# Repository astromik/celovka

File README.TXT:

Astronomická čelovka s červeným a bílým regulovatelným světlem, která je řízená pomocí ATtiny25.

Detaily:
  http://www.astromik.org/raspi/celovka

Video s ukázkou činnosti (verze sw 11):
   https://youtu.be/cCZswjiehJQ

Video s doplněnými funkcemi (verze sw 12):
   https://youtu.be/9VESLbRYwD0

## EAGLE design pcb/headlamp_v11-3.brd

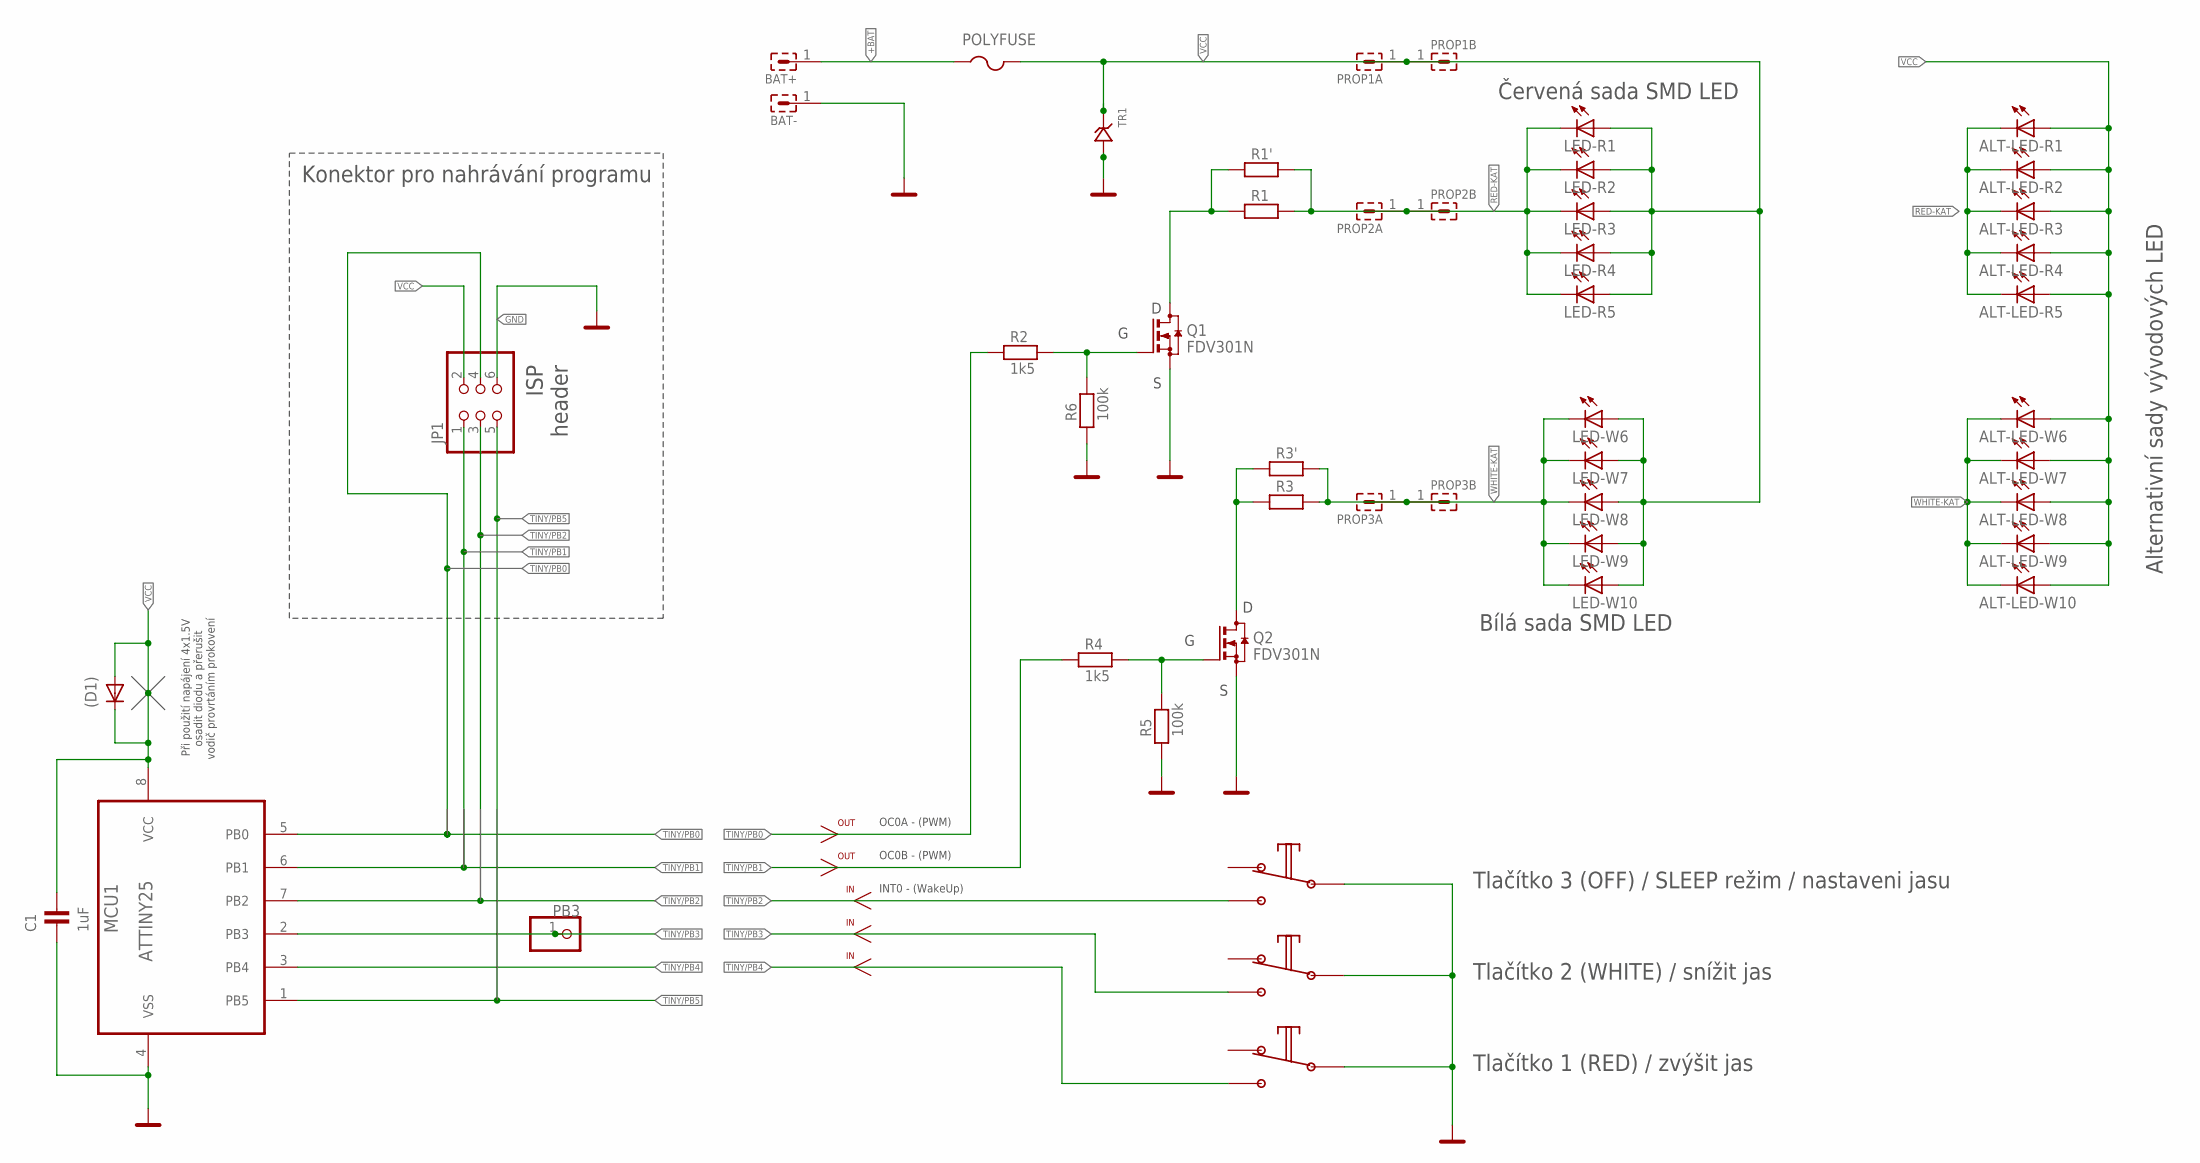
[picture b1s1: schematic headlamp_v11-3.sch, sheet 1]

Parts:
(D1): DIODE-MINIMELF; MINIMELF
ALT-LED-R1, ALT-LED-R2, ALT-LED-R3, ALT-LED-R4, ALT-LED-R5: LED3MM
ALT-LED-W6, ALT-LED-W7, ALT-LED-W8, ALT-LED-W9, ALT-LED-W10: LED3MM
BAT+: S1G1_JUMP; S1G1_JUM
BAT-: S1G1_JUMP; S1G1_JUM
C1: 1uF; 0805
JP1: PINHD-2X3/90; 2X03/90
LED-R1, LED-R2, LED-R3, LED-R4, LED-R5: LEDCHIP-LED0805; CHIP-LED0805
LED-W6, LED-W7, LED-W8, LED-W9, LED-W10: LEDCHIP-LED0805; CHIP-LED0805
MCU1: ATTINY25; SOIC127P600X175-8N
PB3: PINHD-1X1; 1X01
POLYFUSE: PTCFUSE-1812; 1812
PROP1A, PROP1B, PROP2A, PROP2B, PROP3A, PROP3B: S1G1_JUMP; S1G1_JUM
Q1, Q2: FDV301N; SOT23
R1, R3: R_1206; 1206
R1', R3': R_SMD_0805; 0805
R2, R4: 1k5; 0805
R5, R6: 100k; 0805
TLAC1, TLAC2, TLAC3: TLACITKO
TR1: Transil 6V; DO214AC+MINIMELF_BIDIR

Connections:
+BAT: BAT+.1, POLYFUSE.1
GND: BAT-.1, C1.2, JP1.6, MCU1.4 (VSS), Q1.2 (S), Q2.2 (S), R5.1, R6.1, TLAC1.P$1 (COM), TLAC2.P$1 (COM), TLAC3.P$1 (COM), TR1.P$2
RED-DRAIN: Q1.3 (D), R1.1, R1'.2
RED-KAT: ALT-LED-R1.K (C), ALT-LED-R2.K (C), ALT-LED-R3.K (C), ALT-LED-R4.K (C), ALT-LED-R5.K (C), LED-R1.C, LED-R2.C, LED-R3.C, LED-R4.C, LED-R5.C, PROP2A.1, PROP2B.1, R1.2, R1'.1
RED/GATE: Q1.1 (G), R2.2, R6.2
TINY/PB0: JP1.4, MCU1.5 (PB0), R2.1
TINY/PB1: JP1.1, MCU1.6 (PB1), R4.1
TINY/PB2: JP1.3, MCU1.7 (PB2), TLAC3.P$2 (NO)
TINY/PB3: MCU1.2 (PB3), PB3.1, TLAC2.P$2 (NO)
TINY/PB4: MCU1.3 (PB4), TLAC1.P$2 (NO)
TINY/PB5: JP1.5, MCU1.1 (PB5)
VCC: (D1).A, (D1).C, ALT-LED-R1.A, ALT-LED-R2.A, ALT-LED-R3.A, ALT-LED-R4.A, ALT-LED-R5.A, ALT-LED-W6.A, ALT-LED-W7.A, ALT-LED-W8.A, ALT-LED-W9.A, ALT-LED-W10.A, C1.1, JP1.2, LED-R1.A, LED-R2.A, LED-R3.A, LED-R4.A, LED-R5.A, LED-W6.A, LED-W7.A, LED-W8.A, LED-W9.A, LED-W10.A, MCU1.8 (VCC), POLYFUSE.2, PROP1A.1, PROP1B.1, TR1.P$1
WHITE-DRAIN: Q2.3 (D), R3.1, R3'.2
WHITE-KAT: ALT-LED-W6.K (C), ALT-LED-W7.K (C), ALT-LED-W8.K (C), ALT-LED-W9.K (C), ALT-LED-W10.K (C), LED-W6.C, LED-W7.C, LED-W8.C, LED-W9.C, LED-W10.C, PROP3A.1, PROP3B.1, R3.2, R3'.1
WHITE/GATE: Q2.1 (G), R4.2, R5.2

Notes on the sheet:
ISP header
Konektor pro nahrávání programu
OUT
Červená sada SMD LED
Bílá sada SMD LED
Tlačítko 1 (RED) / zvýšit jas
Tlačítko 2 (WHITE) / snížit jas
Tlačítko 3 (OFF) / SLEEP režim / nastaveni jasu
INT0 - (WakeUp)
OC0A - (PWM)
OC0B - (PWM)
Alternativní sady vývodových LED
Při použití napájení 4x1.5V osadit diodu a přerušit vodič provrtáním prokovení

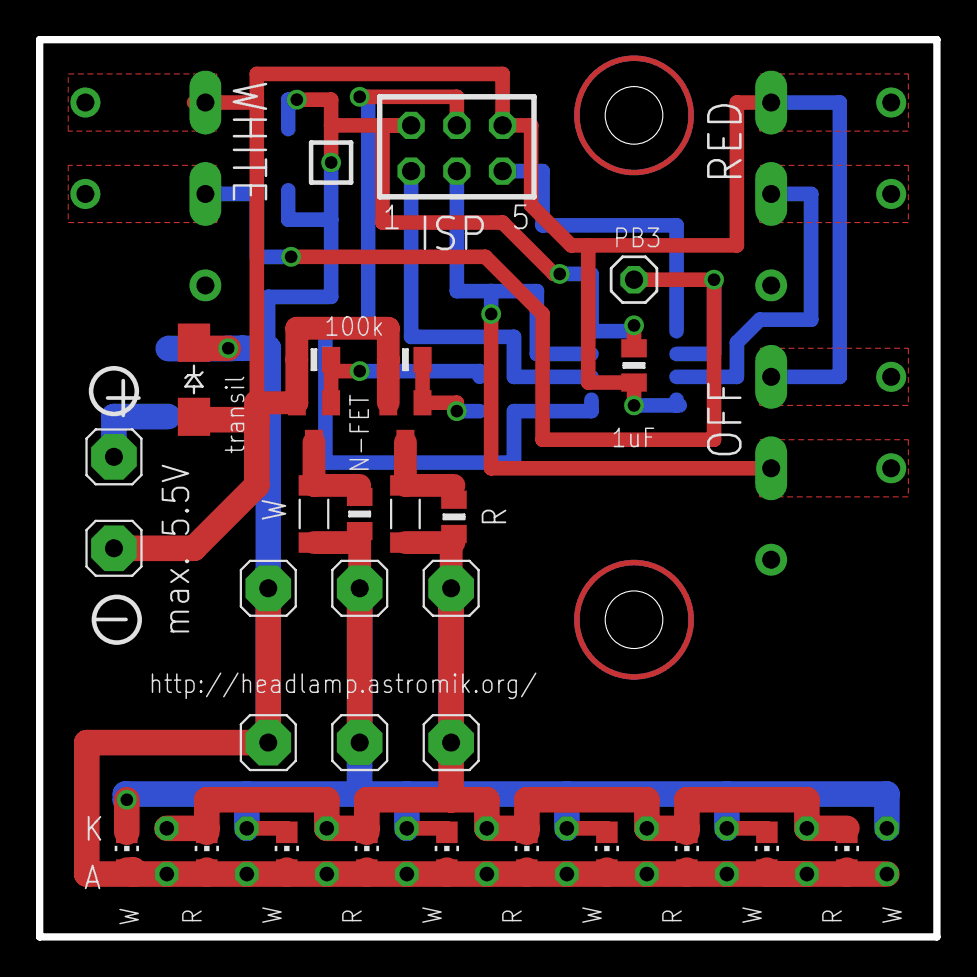
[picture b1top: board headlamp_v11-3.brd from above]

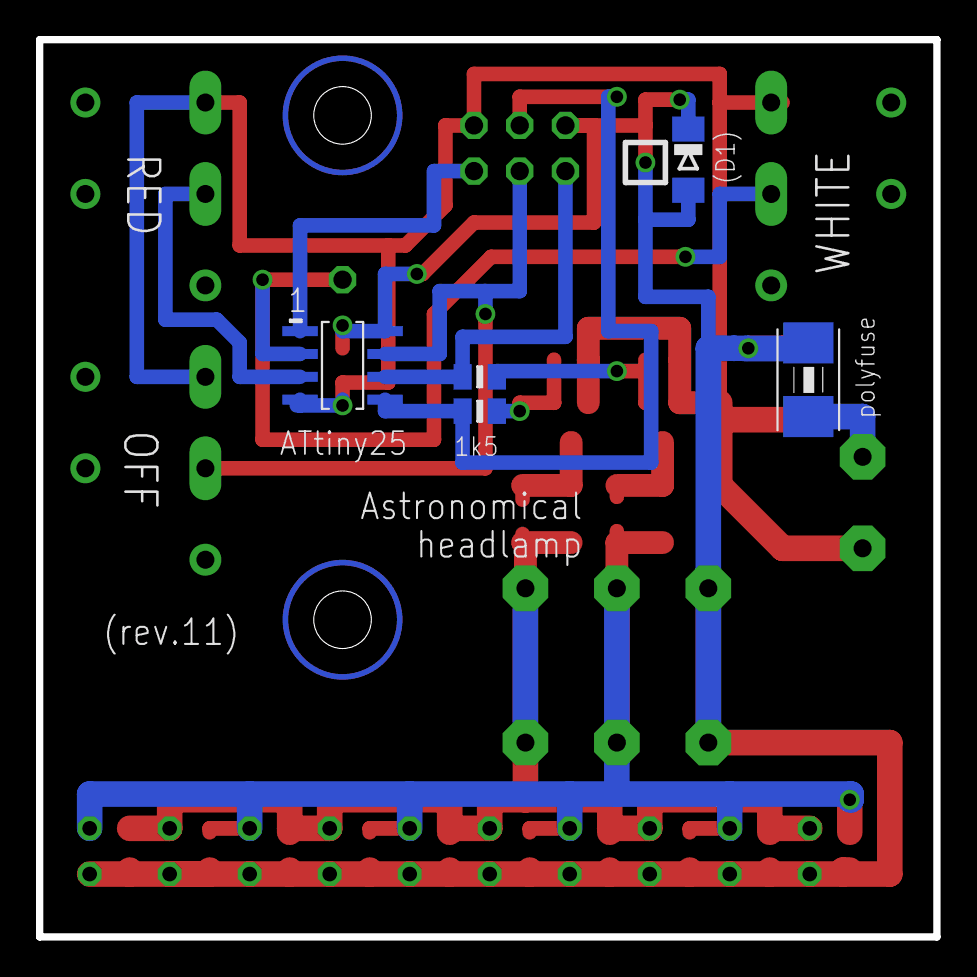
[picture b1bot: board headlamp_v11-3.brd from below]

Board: 2 copper layers, 49.8 x 49.8 mm, 48 parts (6 on the bottom side), 15 nets.

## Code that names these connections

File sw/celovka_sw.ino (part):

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//=============
//                                                  ATtiny25
//                                                   +-\_/-+
//              nezapojeno (RESET)           - PB5  1|     |8  Vcc
//          tlacitko [WHITE] ( / snizit jas) - PB3  2|     |7  PB2  - INT0     - tlacitko [OFF] ( / SLEEP / WAKE-UP)
//            tlacitko [RED] ( / zvysit jas) - PB4  3|     |6  PB1  OC0B (PWM) - bila LED - spinana pres FET
//                                             GND  4|     |5  PB0  OC0A (PWM) - cervena LED - spinana pres FET  
//                                                   +-----+
//
//                   (Tlacitka jsou spinana proti GND, LED jsou kvuli vyssim proudum ovladane pres N-FET napr. 2N7000)
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#include <avr/sleep.h>
#include <stdint.h>

#define tlacitko_RED          0b00010000                         // PB4 tlacitka [RED] a [WHITE] je mozne navzajem prohodit
#define tlacitko_WHITE        0b00001000                         // PB3



#define tlacitko_OFF           0b00000100                         // PB2 kvuli probouzeni pres pevy signal INT0 nelze pozici tlacitka menit

#define STISKNUTO(x)          (!(PINB & (x)))                     // stisknute tlacitko je spojene na GND, takze vraci LOW
#define UVOLNENO(x)             (PINB & (x))                      // uvolnene tlacitko je pull-upovane, takze vraci HIGH
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}

// ===================================================================
// rozsviceni cervene LED (PWM kanal A - pin PB0)
// parametrem je index pole logaritmy[]  ; 0 az 9 odpovida 10% az 100% jasu
void red_on(byte level_red)
  {
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

// ===================================================================
// rozsviceni bile LED (PWM kanal B - pin PB1)
// parametrem je index pole logaritmy[]  ; 0 az 9 odpovida 10% az 100% jasu
void white_on(byte WHITE)
  {
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  }

// ===================================================================
// bez parametru se postupne rozsviti bila sada LED (PWM kanal B - pin PB1) na posledni nastaveny jas bile LED
void white_on(void)
  {
    byte zkratka = 0;
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// signalizace stavu baterie bliknutim LED
void test_napeti(void)
  {
    while (true)                                                  // nekonecna blikaci smycka se prerusi jen stiskem tlacitka na PB2 behem vyckavacich pauz
      {
        uint8_t bat = getBatteryLevel();                          // stav baterie (1=slaba .... 4=plna)
        
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
                                                                  // nastaveni smeru portu a Pull-Upu
    DDRB  = 0b00000011;                                           // nastaveni smeru signalu na portu B ("1" = vystup ; "0" = vstup)
    PORTB = 0b00011111;                                           // na vsechny tlacitka (PB2, PB3 a PB4) Pull-Upy a oba vystupy (PB0, PB1) zhasnout

                                                                  // nastaveni rezimu PWM
    TCCR0A = 0b11110011;                                          // rezim FAST PWM; vystup se nastavi do '0' pri dosazeni pozadovaneho cisla
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             
          while (zamek == 1)                                      // dokud je platny pozadavek na uspani (dokud nebylo odemceno dlouhym stiskem, tak se po kazdem probuzeni zase ATtiny uspi)
            { 
              sleep();                                            // uspani do doby, nez dojde k sestupne hrane impulzu na INT0 (PB2)
              delay(wakeup_timer);                                // 0.1 sekundy pauza po probuzeni
              
              starttime = millis();                               // cas probuzeni se zapamatuje
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
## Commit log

2017-02-04 ver. 11
2017-02-04 ver. 12
2026-05-28 Verze 13
    Verze čelovky s měřením napětí napájecí baterie.
    Byl zrušen výběr typu blikání ve funkci BLIKAČ.
    Při rozsvícené bílé sadě LED je tlačítko WHITE zhasne.
    Zjednodušená možnost prohození tlačítek RED a WHITE úpravou dvou řádek v programu.
    Tajná funkce pro přepnutí na pomalé rozsvěcení bílé sady LED (postup popsán v komentáři uvnitř programu).
2026-05-28 Doplnění nastavení Arduino IDE
    Obrázky s nastavením pro ATtiny25
2026-05-28 Aktualizace obrázků IDE
    Změny v obrázcích nastavení Arduino IDE

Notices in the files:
parts and their libraries:
Copyright (C) PaJa 2001-2011
sirsi_pin: Copyright (C) PaJa 2011-2014
Copyright (C) PaJa 2001-2014
